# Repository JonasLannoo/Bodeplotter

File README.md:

# Bodeplotter
Bodeplotter HAT for NUCLEO_L476RG

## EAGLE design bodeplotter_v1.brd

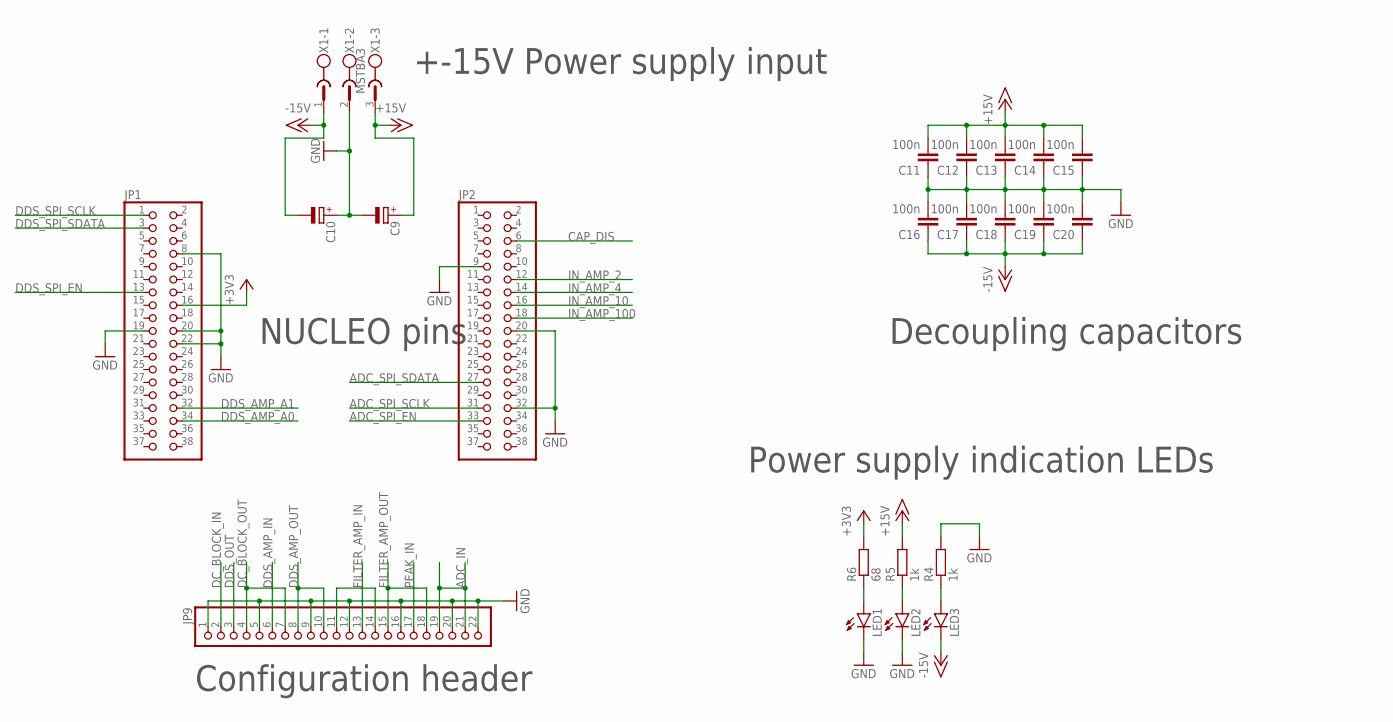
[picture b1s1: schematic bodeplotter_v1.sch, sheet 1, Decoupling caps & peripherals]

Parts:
C9, C10: CPOL-EU140CLH-0810; 140CLH-0810
C11, C12, C13, C14, C15, C16, C17, C18, C19, C20: 100n; C0805
JP1, JP2: PINHD-2X19; 2X19
JP9: PINHD-1X22; 1X22
LED1, LED2, LED3: LEDCHIPLED_1206; CHIPLED_1206
R4, R5: 1k; R0805
R6: 68; R0805
X1: MSTBA3

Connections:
+3V3: JP1.16, R6.2; also elsewhere on the board
+15V: C9.+, C11.2, C12.2, C13.2, C14.2, C15.2, R5.2, X1.3; also elsewhere on the board
-15V: C10.-, C16.1, C17.1, C18.1, C19.1, C20.1, LED3.C, X1.1; also elsewhere on the board
ADC_IN: JP9.19, JP9.21; also elsewhere on the board
ADC_SPI_EN: JP2.33; also elsewhere on the board
ADC_SPI_SCLK: JP2.31; also elsewhere on the board
ADC_SPI_SDATA: JP2.27; also elsewhere on the board
CAP_DIS: JP2.6; also elsewhere on the board
DC_BLOCK_IN: JP9.2; also elsewhere on the board
DC_BLOCK_OUT: JP9.4, JP9.7; also elsewhere on the board
DDS_AMP_A0: JP1.34; also elsewhere on the board
DDS_AMP_A1: JP1.32; also elsewhere on the board
DDS_AMP_IN: JP9.6; also elsewhere on the board
DDS_AMP_OUT: JP9.8, JP9.10; also elsewhere on the board
DDS_OUT: JP9.3; also elsewhere on the board
DDS_SPI_EN: JP1.13; also elsewhere on the board
DDS_SPI_SCLK: JP1.1; also elsewhere on the board
DDS_SPI_SDATA: JP1.3; also elsewhere on the board
FILTER_AMP_IN: JP9.13; also elsewhere on the board
FILTER_AMP_OUT: JP9.15, JP9.18; also elsewhere on the board
GND: C9.-, C10.+, C11.1, C12.1, C13.1, C14.1, C15.1, C16.2, C17.2, C18.2, C19.2, C20.2, JP1.8, JP1.19, JP1.20, JP1.22, JP2.9, JP2.20, JP2.32, JP9.1, JP9.5, JP9.9, JP9.12, JP9.16, JP9.20, JP9.22, LED1.C, LED2.C, R4.2, X1.2; also elsewhere on the board
IN_AMP_2: JP2.12; also elsewhere on the board
IN_AMP_4: JP2.14; also elsewhere on the board
IN_AMP_10: JP2.16; also elsewhere on the board
IN_AMP_100: JP2.18; also elsewhere on the board
unnamed: LED1.A, R6.1
unnamed: LED2.A, R5.1
unnamed: LED3.A, R4.1
unnamed: JP9.11, JP9.14
PEAK_IN: JP9.17; also elsewhere on the board

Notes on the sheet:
+-15V Power supply input
NUCLEO pins
Configuration header
Power supply indication LEDs
Decoupling capacitors

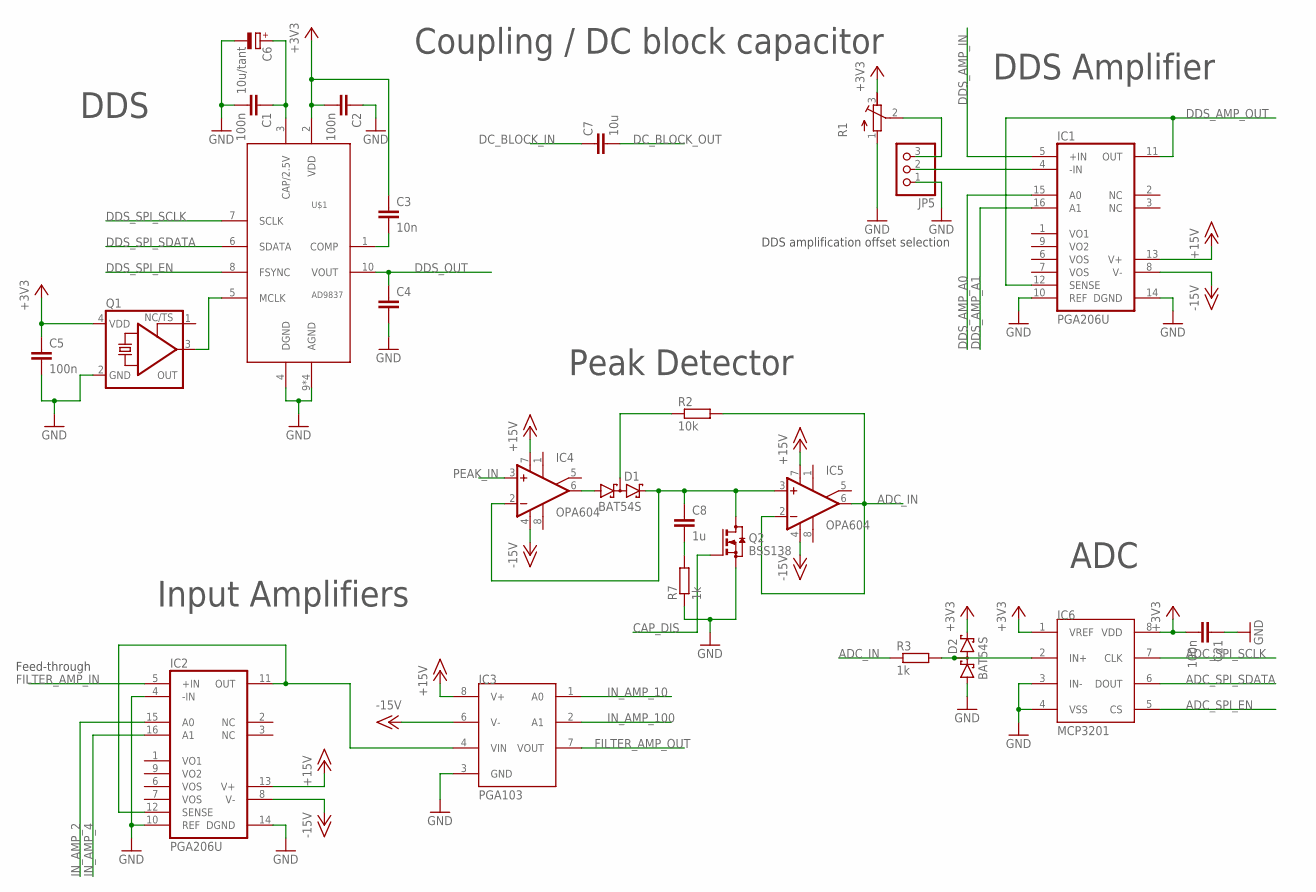
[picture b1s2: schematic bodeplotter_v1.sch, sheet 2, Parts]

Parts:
C1, C2, C5, C21: 100n; C0805
C3: 10n; C0805
C4: C-EUC0805; C0805
C6: 10u/tant; CT6032
C7: 10u; C0805
C8: 1u; C0805
D1, D2: BAT54S; SOT23
IC1, IC2: PGA206U; SO16-1
IC3: PGA103; SOIC8
IC4, IC5: OPA604; DIL08
IC6: MCP3201; SOIC8
JP5: PINHD-1X3; 1X03
Q1: KXO-PXO/XO-V95; 2.5X2.0_KXO-V95
Q2: BSS138; SOT23
R1: R-TRIMM64W; RTRIM64W
R2: 10k; R0805
R3, R7: 1k; R0805
U$1: AD9837; ANALOG_DEVICES_AD5667BCPZ-R2_2

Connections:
+3V3: C2.2, C3.1, C5.1, C21.2, D2.2 (C2), IC6.1 (VREF), IC6.8 (VDD), Q1.4 (VDD), R1.3 (E), U$1.2 (VDD); also elsewhere on the board
+15V: IC1.13 (V+), IC2.13 (V+), IC3.8 (V+), IC4.7 (V+), IC5.7 (V+); also elsewhere on the board
-15V: IC1.8 (V-), IC2.8 (V-), IC3.6 (V-), IC4.4 (V-), IC5.4 (V-); also elsewhere on the board
ADC_IN: IC5.2 (-IN), IC5.6 (OUT), R2.2, R3.1; also elsewhere on the board
ADC_SPI_EN: IC6.5 (CS); also elsewhere on the board
ADC_SPI_SCLK: IC6.7 (CLK); also elsewhere on the board
ADC_SPI_SDATA: IC6.6 (DOUT); also elsewhere on the board
CAP_DIS: Q2.1 (G); also elsewhere on the board
DC_BLOCK_IN: C7.1; also elsewhere on the board
DC_BLOCK_OUT: C7.2; also elsewhere on the board
DDS_AMP_A0: IC1.15 (A0); also elsewhere on the board
DDS_AMP_A1: IC1.16 (A1); also elsewhere on the board
DDS_AMP_IN: IC1.5 (+IN); also elsewhere on the board
DDS_AMP_OUT: IC1.11 (OUT), IC1.12 (SENSE); also elsewhere on the board
DDS_OUT: C4.1, U$1.10 (VOUT); also elsewhere on the board
DDS_SPI_EN: U$1.8 (FSYNC); also elsewhere on the board
DDS_SPI_SCLK: U$1.7 (SCLK); also elsewhere on the board
DDS_SPI_SDATA: U$1.6 (SDATA); also elsewhere on the board
FILTER_AMP_IN: IC2.5 (+IN); also elsewhere on the board
FILTER_AMP_OUT: IC3.7 (VOUT); also elsewhere on the board
GND: C1.2, C2.1, C4.2, C5.2, C6.-, C21.1, D2.1 (A1), IC1.10 (REF), IC1.14 (DGND), IC2.4 (-IN), IC2.10 (REF), IC2.14 (DGND), IC3.3 (GND), IC6.3 (IN-), IC6.4 (VSS), JP5.1, Q1.2 (GND), Q2.2 (S), R1.1 (A), R7.1, U$1.4 (DGND), U$1.9 (AGND), U$1.11 (AGND), U$1.PAD_1 (AGND), U$1.PAD_2 (AGND); also elsewhere on the board
IN_AMP_2: IC2.15 (A0); also elsewhere on the board
IN_AMP_4: IC2.16 (A1); also elsewhere on the board
IN_AMP_10: IC3.1 (A0); also elsewhere on the board
IN_AMP_100: IC3.2 (A1); also elsewhere on the board
unnamed: D2.3 (C1A2), IC6.2 (IN+), R3.2
unnamed: C3.2, U$1.1 (COMP)
unnamed: C1.1, C6.+, U$1.3 (CAP/2.5V)
unnamed: IC1.4 (-IN), JP5.2
unnamed: Q1.3 (OUT), U$1.5 (MCLK)
unnamed: JP5.3, R1.2 (S)
unnamed: C8.2, R7.2
unnamed: D1.3 (C1A2), R2.1
unnamed: IC2.11 (OUT), IC2.12 (SENSE), IC3.4 (VIN)
unnamed: D1.1 (A1), IC4.6 (OUT)
unnamed: C8.1, D1.2 (C2), IC4.2 (-IN), IC5.3 (+IN), Q2.3 (D)
PEAK_IN: IC4.3 (+IN); also elsewhere on the board

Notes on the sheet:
Feed-through
DDS amplification offset selection
ADC
Peak Detector
DDS
Coupling / DC block capacitor
DDS Amplifier
Input Amplifiers

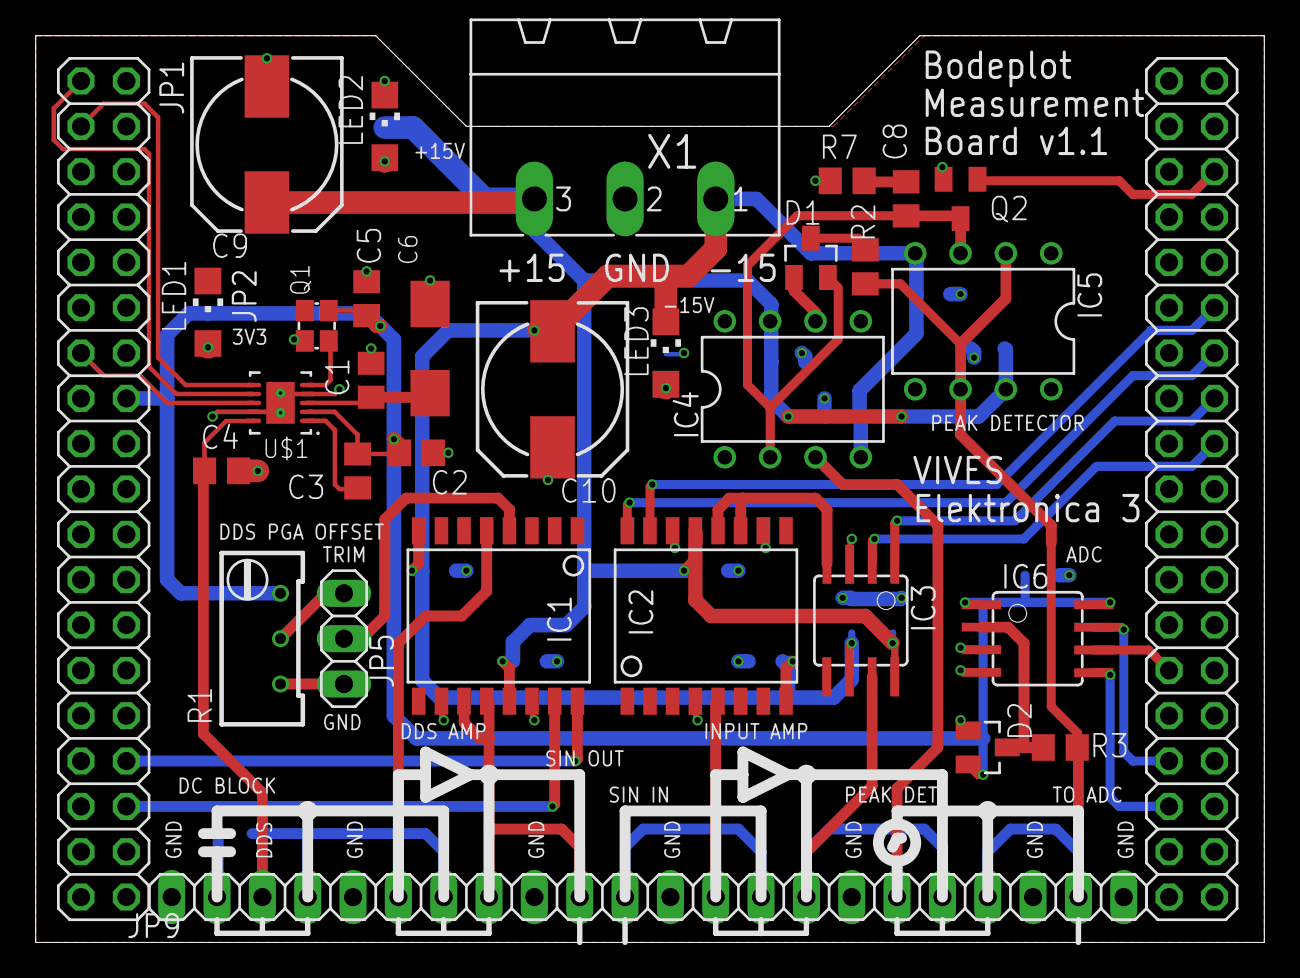
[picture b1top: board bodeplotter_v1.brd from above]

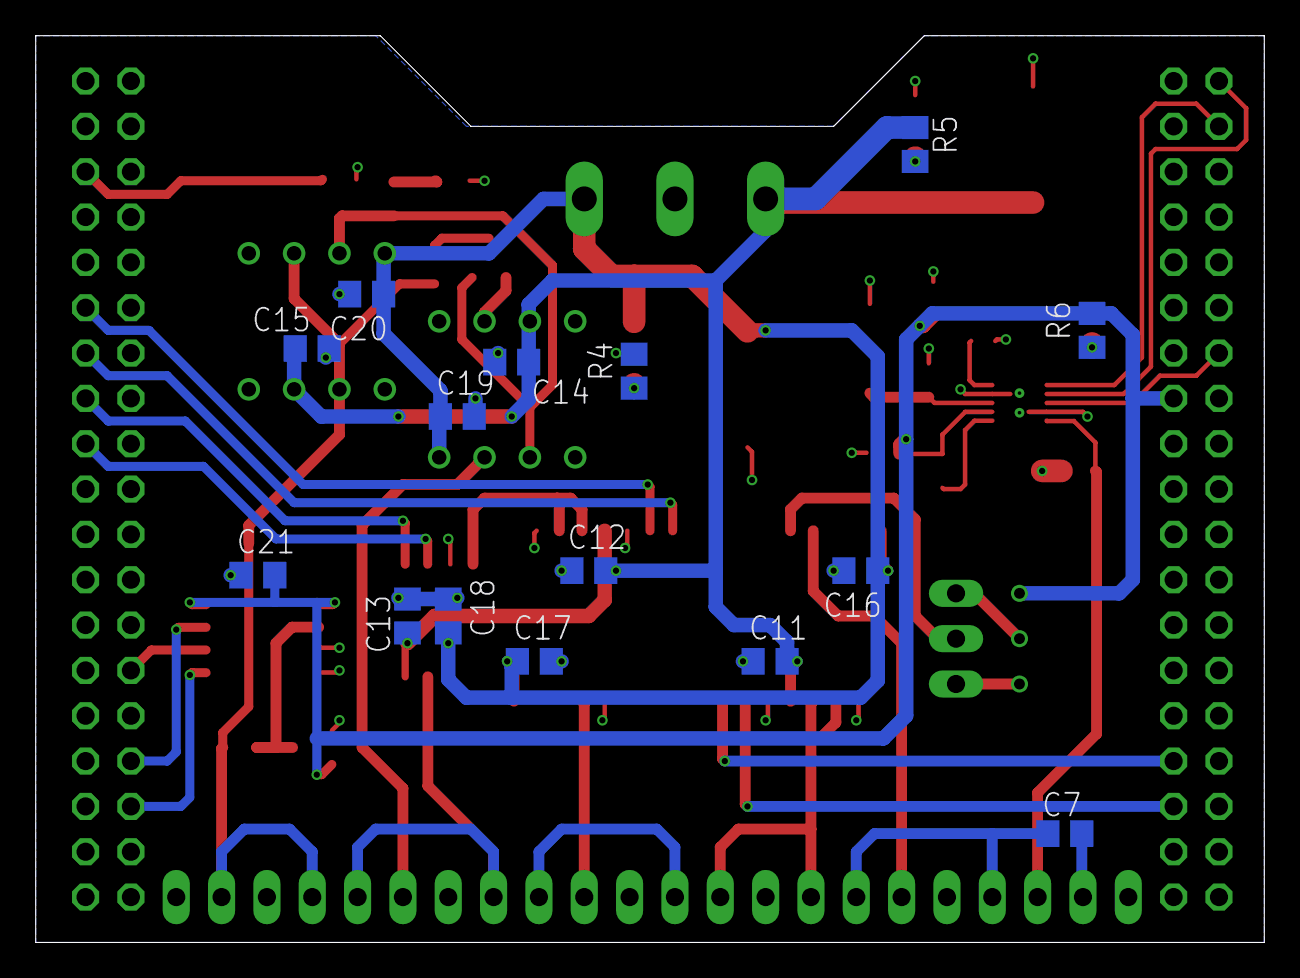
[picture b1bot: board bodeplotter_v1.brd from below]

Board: 2 copper layers, 68.8 x 50.8 mm, 47 parts (15 on the bottom side), 41 nets.

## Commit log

2021-11-23 initial files added
2021-11-25 soldered version

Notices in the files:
parts and their libraries:
crystal-geyer_V1_0: Copyright: Geyer-Electronic
